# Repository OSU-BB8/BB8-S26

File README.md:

# BB8-S26
Welcome to the BB8 project! This repo has all the files that we used to develop the BB8 as well as a ton of old files from previous groups.

To test out the project, a few things need to be done first.

1. Plug the Pi on the main BB8 (Not the test one in the chassis) to a power source
2. You will need to connect the Pi to a monitor to find out its IP address and connect it to eduroam or whichever network you want to use.
3. The robot has two modes right now: The PS5 controller mode and the head-body communication mode that reads april tags.

PS5 Controller Mode:
1. Pair the PS5 controller with the body Pi (The one in the sphere). You can do this from the terminal or GUI
2. Plug in the 24V LiPo battery to the robot. This connects to everything except the Pi (which is a Pi 4B - definitely could use the upgrade to a 5, which should be in the materials).
3. Plug in the 3.7V with boost converter into the Pi and disconnect anything external from it.
4. Connect the shell so that it encapsulates the entire robot.
5. SSH into the body Pi. The user is "bb8" and password is "password" (I know right).
6. Navigate to /'BB8 Files'/'Body Files' 
7. Run the python files "PS5_Controller.py"
8. This will give you a menu of options to select. The two main ones are options 5 and 6. Choose 5 if you want the option that will balance the head and balance the body (Although the pendulum body balancer doesn't work well since the PID values are 0 for now). Option 6 gives the user full control over all the motors and functions.

Head-Body Communication:
1.You'll want to power up the head's Pi. This can be found on the picar, which we used for testing and then placed inside the head for Demo purposes.
2. Plug in the Head's Pi and navigate to the terminal. Form here, you should look at the terminal and find out the IP address.
3. Instead of pairing the PS5 Controller, go to the file "Expo_Demo.py" in 'BB8 Files'/'Expo Demo'. Replace the IP address in it with the new body IP address.
4. Make sure both the Body and the Head Pi's are turned on. 
5. Run Body_communication.py ON THE BODY. This opens up a UDP socket and waits for commands from the head.
6. Run Head_Communication.py ON THE HEAD. This allows you to send commands from the head to the body.
7. If you want to SSH into the head Pi, the user is "bb8camera" and the password is "password".

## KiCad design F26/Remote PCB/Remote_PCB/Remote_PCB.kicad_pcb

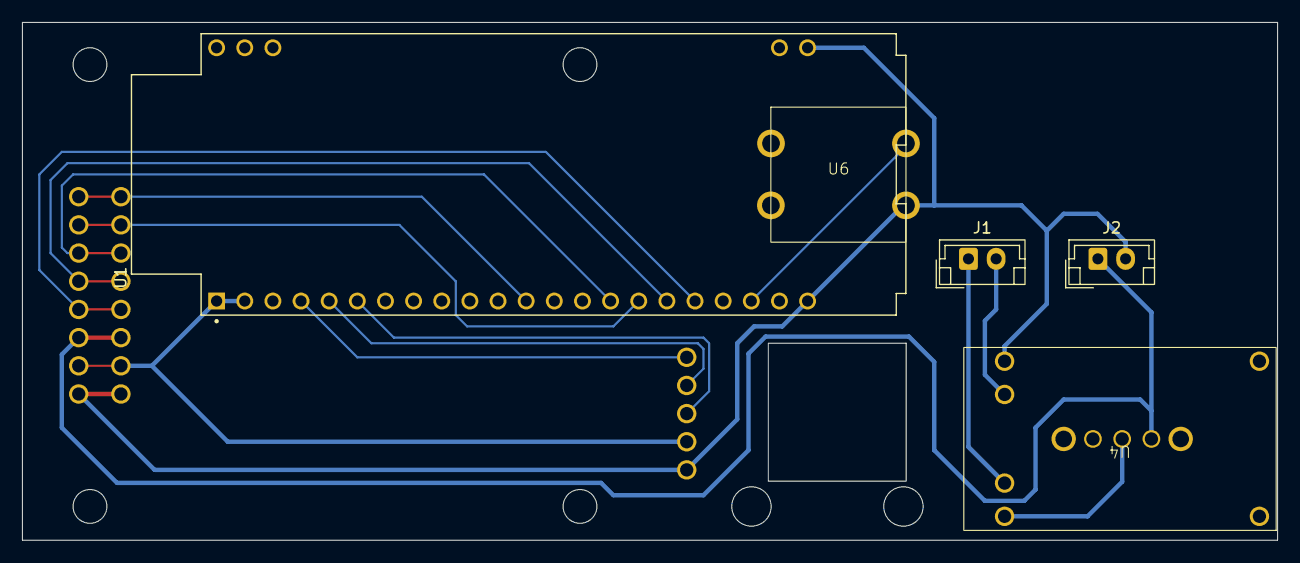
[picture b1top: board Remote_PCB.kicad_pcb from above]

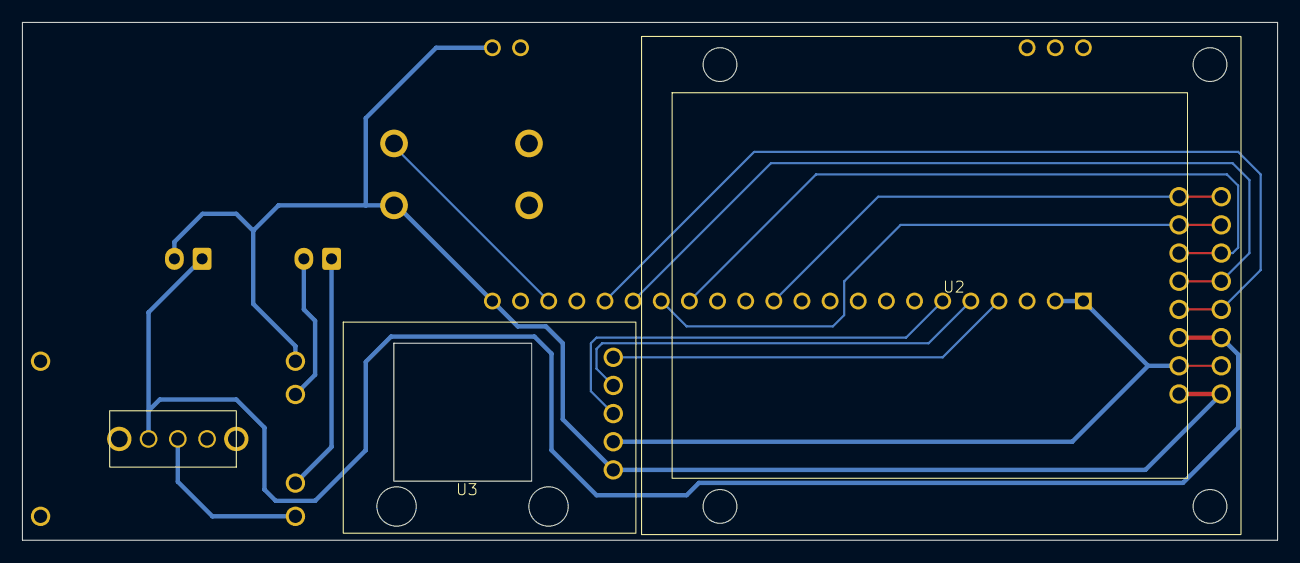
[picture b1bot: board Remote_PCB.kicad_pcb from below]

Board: 2 copper layers, 113.3 x 46.7 mm, 8 parts (3 on the bottom side), 15 nets.

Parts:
J1, J2: B2B-XH-A; JST_EH_B2B-EH-A_1x02_P2.50mm_Vertical
SW1: SW_Nidec_CAS-120A1; Button_Switch_SMDNidec_Copal_CAS-120A
U1: MODULE_ESP32-S2-DEVKITC-1
U2: 1.8 TFT MODULE
U3: Rotary Encoder
U4: Battery Module
U6: Button

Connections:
unnamed: J2.1, SW1.3 (A), U2.6 (VCC)
unnamed: SW1.2 (B), U4.3 (OUT+)
unnamed: U1.4 (GPIO4), U3.1 (CLK)
unnamed: U1.5 (GPIO5), U3.2 (DT)
unnamed: U1.6 (GPIO6), U3.3 (SW)
unnamed: U1.12 (GPIO8), U2.1 (RST)
unnamed: U1.15 (GPIO9), U2.3 (D/C)
unnamed: U1.16 (GPIO10), U2.2 (CS)
unnamed: U1.17 (GPIO11), U2.4 (DIN)
unnamed: U1.18 (GPIO12), U2.5 (CLK)
unnamed: U1.20 (GPIO14), U6.1 (L1)
unnamed: U1.1 (3V3), U1.2 (3V3), U2.7 (BL), U3.4 (+)
unnamed: J2.2, U1.22 (GND), U1.23 (GND), U2.8 (GND), U3.5 (GND), U4.6 (OUT-), U6.2 (L2)
unnamed: J1.1, U4.4 (B+)
unnamed: J1.2, U4.5 (B-)

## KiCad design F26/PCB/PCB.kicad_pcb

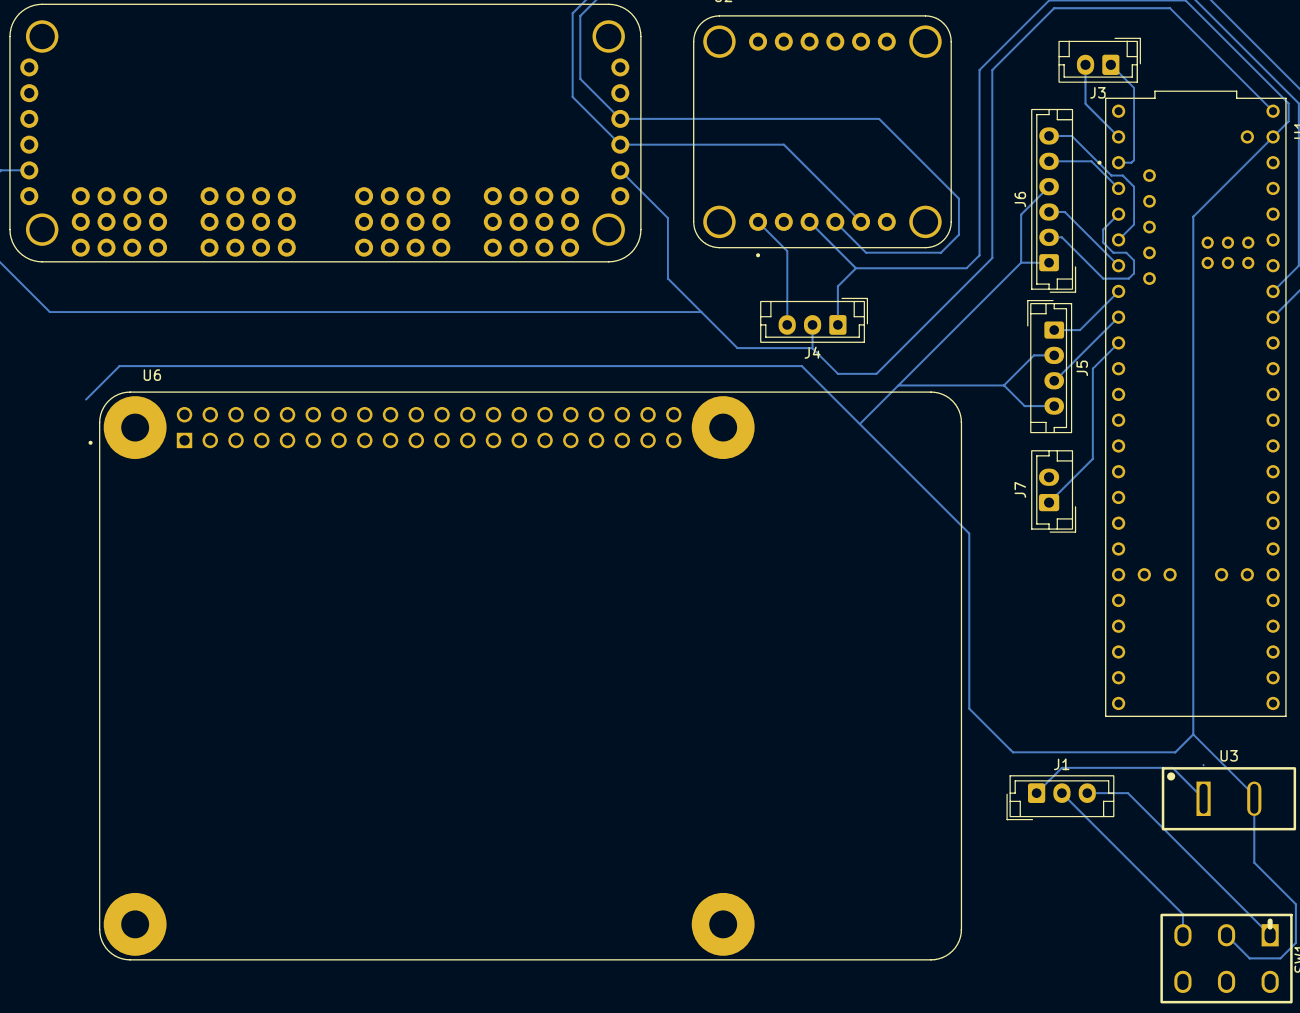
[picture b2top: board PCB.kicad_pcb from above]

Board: 2 copper layers, 12 parts (0 on the bottom side), 23 nets.

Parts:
J1, J4: B3B-XH-A; JST_EH_B3B-EH-A_1x03_P2.50mm_Vertical
J3: B2B-XH-A; JST_EH_B2B-EH-A_1x02_P2.50mm_Vertical
J5: Conn_01x04; JST_EH_B4B-EH-A_1x04_P2.50mm_Vertical
J6: Conn_01x06; JST_EH_B6B-EH-A_1x06_P2.50mm_Vertical
J7: Conn_01x02; JST_EH_B2B-EH-A_1x02_P2.50mm_Vertical
SW1: SW_Nidec_CAS-120A1; Mini_Toggle_DPDT_4.3x4.6mm
U1: Teensy
U2: MODULE_BNO085
U3: Switch_2Pin_5mm_ParallelBlades
U4: 815; MODULE_PCA9685
U6: SC0194_9_; MODULE_SC0194_9_

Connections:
3V3: U6.1 (3V3), U6.17 (3V3)
5V0: U6.2 (5V0), U6.4 (5V0)
GND: U4.GND_1 (GND), U4.GND_2 (GND), U4.GND_3 (GND), U4.GND_4 (GND), U4.GND_5 (GND), U4.GND_6 (GND), U4.GND_7 (GND), U4.GND_8 (GND), U4.GND_9 (GND), U4.GND_10 (GND), U4.GND_11 (GND), U4.GND_12 (GND), U4.GND_13 (GND), U4.GND_14 (GND), U4.GND_15 (GND), U4.GND_16 (GND), U4.GND_17 (GND), U4.GND_18 (GND), U6.6 (GND), U6.9 (GND), U6.14 (GND), U6.20 (GND), U6.25 (GND), U6.30 (GND), U6.34 (GND), U6.39 (GND)
unnamed: J1.1, U3.1
unnamed: J5.1, U1.6 (OUT1D)
unnamed: J4.1, J5.2, J5.4, J6.1, J6.4, SW1.2 (B), U1.GND, U2.3 (GND), U3.2
unnamed: J5.3, U1.7 (OUT1A)
unnamed: J6.2, U1.3 (LRCLK2)
unnamed: J6.3, U1.5 (IN2)
unnamed: J6.5, U1.2 (OUT2)
unnamed: J6.6, U1.4 (BCLK2)
unnamed: J7.1 (Pin_1_1), U1.8 (IN1)
unnamed: J1.2, SW1.3 (A)
unnamed: J1.3, SW1.1 (C)
unnamed: U1.18 (A4), U2.5 (SDA), U4.SDA_1 (SDA), U4.SDA_2 (SDA)
unnamed: U1.19 (A5), U2.4 (SCL), U4.SCL_1 (SCL), U4.SCL_2 (SCL)
unnamed: J3.2, U1.0 (RX1)
unnamed: J3.1, U1.1 (TX1)
unnamed: J4.3, U2.1 (VIN)
unnamed: U4.OE_1 (~OE), U4.OE_2 (~OE)
SHIELD: U6.S1 (SHIELD), U6.S2 (SHIELD), U6.S3 (SHIELD), U6.S4 (SHIELD)
V+: U4.V+_1 (V+), U4.V+_2 (V+), U4.V+_3 (V+), U4.V+_4 (V+), U4.V+_5 (V+), U4.V+_6 (V+), U4.V+_7 (V+), U4.V+_8 (V+), U4.V+_9 (V+), U4.V+_10 (V+), U4.V+_11 (V+), U4.V+_12 (V+), U4.V+_13 (V+), U4.V+_14 (V+), U4.V+_15 (V+), U4.V+_16 (V+), U4.V+_17 (V+), U4.V+_18 (V+)
VCC: J4.2, U1.Vin, U4.VCC_1 (VCC), U4.VCC_2 (VCC)

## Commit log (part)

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2026-04-30 Import of all pertinent files from the S26 semester.
2026-04-30 Folder Reorganizations.
2026-04-30 Added Electrical Flowchart
2026-04-30 Update hardcoded Body Pi IP address
2026-04-30 Enhance README with setup and usage instructions
    Expanded README with detailed setup instructions for BB8 project, including PS5 controller mode and head-body communication mode.
2026-05-04 Add guide to the archive directory
2026-05-04 Update Guide with additional information
2026-05-04 Revise guide text for directory clarity
    Updated the description of the directory and removed obsolete information.
2026-05-04 Create guide for directory contents
    Added a guide explaining the contents of the directory.
2026-05-04 Add guide for files in Body Files directory
    Added a guide explaining the purpose of files in the directory, including Body_Communication, Dead_Reckoning, IMU, Movement_Functions, PID, and PS5_Controller.
2026-05-04 Rename Guide to Guide.md
2026-05-04 Create Guide.md file
2026-05-04 Update guide formatting and content
2026-05-04 Update README with head-body communication steps
    Reordered steps for head-body communication and added details.
2026-05-04 Change SSH user for body Pi and add head Pi SSH info
    Updated SSH user for body Pi and added SSH details for head Pi.
